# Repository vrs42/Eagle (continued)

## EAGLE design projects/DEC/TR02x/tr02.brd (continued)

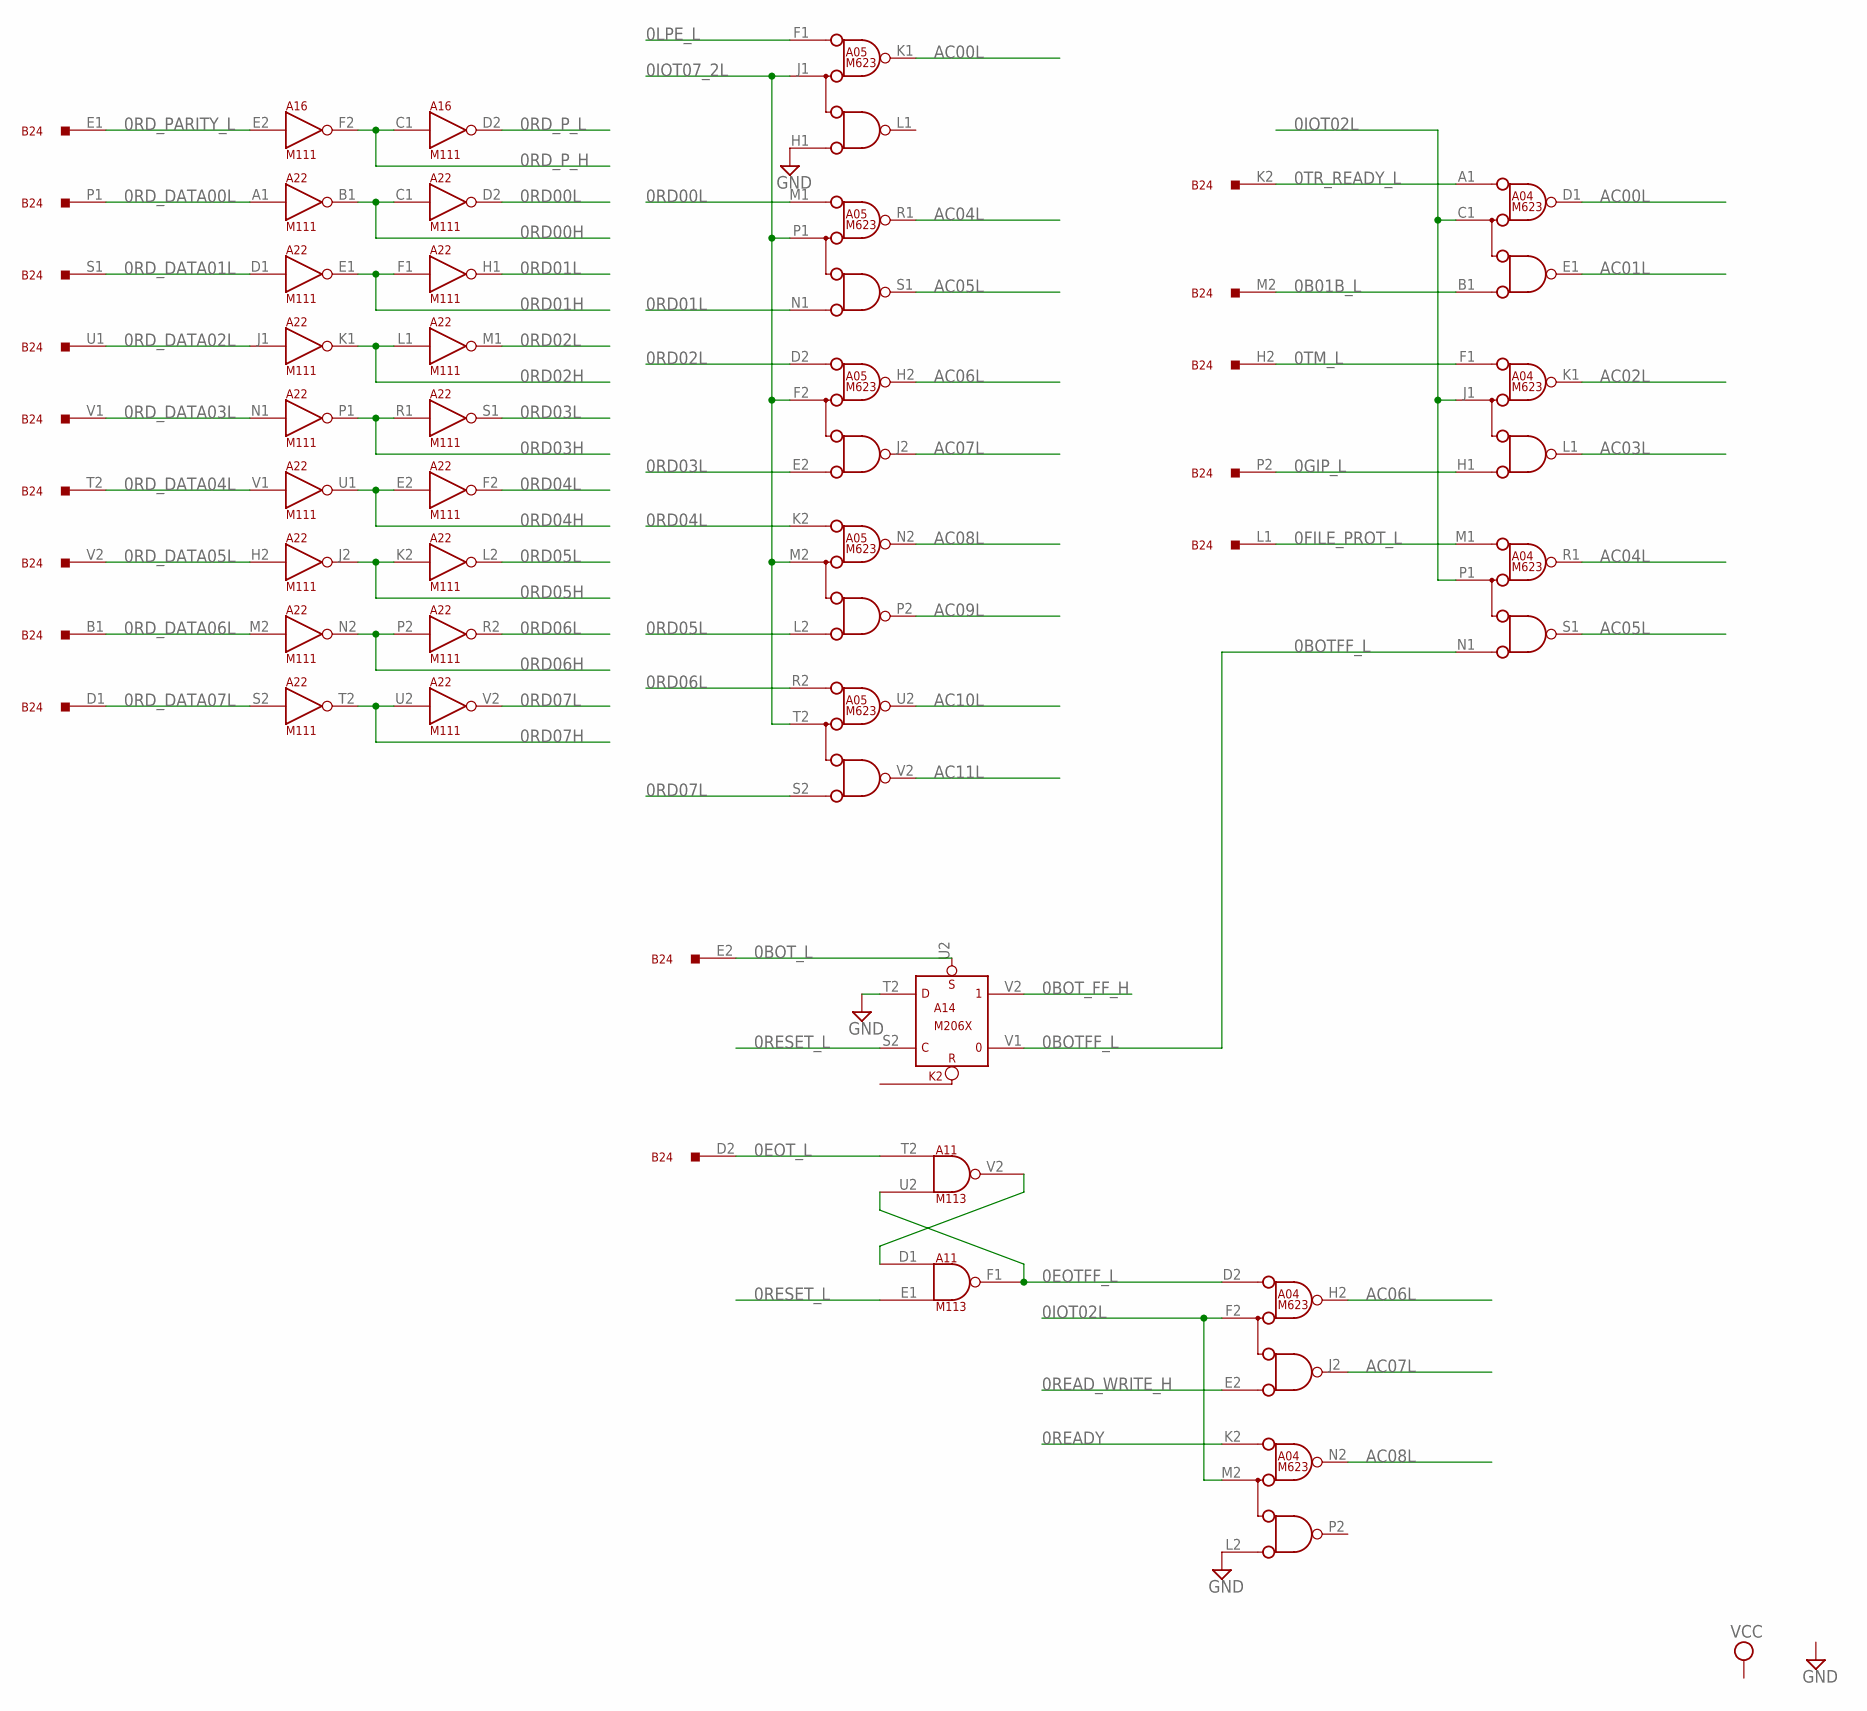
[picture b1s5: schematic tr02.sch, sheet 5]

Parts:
A04, A05: M623; H807
A11: M113; H807
A14: M206X; H807
A16, A22: M111; H807
B24: G784; H807

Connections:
0B01B_L: A04.B1 (B), B24.M2
0BOTFF_L: A04.N1 (B), A14.V1 (0)
0BOT_FF_H: A14.V2 (1); also elsewhere on the board
0BOT_L: A14.U2 (S), B24.E2; also elsewhere on the board
0EOTFF_L: A04.D2 (A), A11.F1 (OUT), A11.U2 (IN2)
0EOT_L: A11.T2 (IN1), B24.D2
0FILE_PROT_L: A04.M1 (A), B24.L1
0GIP_L: A04.H1 (B), B24.P2; also elsewhere on the board
0IOT02L: A04.C1 (C), A04.F2 (C), A04.J1 (C), A04.M2 (C), A04.P1 (C); also elsewhere on the board
0IOT07_2L: A05.F2 (C), A05.J1 (C), A05.M2 (C), A05.P1 (C), A05.T2 (C); also elsewhere on the board
0LPE_L: A05.F1 (A); also elsewhere on the board
0RD00H: A22.B1 (OUT), A22.C1 (IN); also elsewhere on the board
0RD00L: A05.M1 (A), A22.D2 (OUT); also elsewhere on the board
0RD01H: A22.E1 (OUT), A22.F1 (IN); also elsewhere on the board
0RD01L: A05.N1 (B), A22.H1 (OUT); also elsewhere on the board
0RD02H: A22.K1 (OUT), A22.L1 (IN); also elsewhere on the board
0RD02L: A05.D2 (A), A22.M1 (OUT); also elsewhere on the board
0RD03H: A22.P1 (OUT), A22.R1 (IN); also elsewhere on the board
0RD03L: A05.E2 (B), A22.S1 (OUT); also elsewhere on the board
0RD04H: A22.E2 (IN), A22.U1 (OUT); also elsewhere on the board
0RD04L: A05.K2 (A), A22.F2 (OUT); also elsewhere on the board
0RD05H: A22.J2 (OUT), A22.K2 (IN); also elsewhere on the board
0RD05L: A05.L2 (B), A22.L2 (OUT); also elsewhere on the board
0RD06H: A22.N2 (OUT), A22.P2 (IN); also elsewhere on the board
0RD06L: A05.R2 (A), A22.R2 (OUT); also elsewhere on the board
0RD07H: A22.T2 (OUT), A22.U2 (IN); also elsewhere on the board
0RD07L: A05.S2 (B), A22.V2 (OUT); also elsewhere on the board
0RD_DATA00L: A22.A1 (IN), B24.P1
0RD_DATA01L: A22.D1 (IN), B24.S1
0RD_DATA02L: A22.J1 (IN), B24.U1
0RD_DATA03L: A22.N1 (IN), B24.V1
0RD_DATA04L: A22.V1 (IN), B24.T2
0RD_DATA05L: A22.H2 (IN), B24.V2
0RD_DATA06L: A22.M2 (IN), B24.B1
0RD_DATA07L: A22.S2 (IN), B24.D1
0RD_PARITY_L: A16.E2 (IN), B24.E1
0RD_P_H: A16.C1 (IN), A16.F2 (OUT); also elsewhere on the board
0RD_P_L: A16.D2 (OUT)
0READY: A04.K2 (A)
0READ_WRITE_H: A04.E2 (B); also elsewhere on the board
0RESET_L: A11.E1 (IN2), A14.S2 (C); also elsewhere on the board
0TM_L: A04.F1 (A), B24.H2
0TR_READY_L: A04.A1 (A), B24.K2; also elsewhere on the board
AC00L: A04.D1 (D), A05.K1 (D); also elsewhere on the board
AC01L: A04.E1 (E); also elsewhere on the board
AC02L: A04.K1 (D); also elsewhere on the board
AC03L: A04.L1 (E); also elsewhere on the board
AC04L: A04.R1 (D), A05.R1 (D); also elsewhere on the board
AC05L: A04.S1 (E), A05.S1 (E); also elsewhere on the board
AC06L: A04.H2 (D), A05.H2 (D); also elsewhere on the board
AC07L: A04.J2 (E), A05.J2 (E); also elsewhere on the board
AC08L: A04.N2 (D), A05.N2 (D); also elsewhere on the board
AC09L: A05.P2 (E); also elsewhere on the board
AC10L: A05.U2 (D); also elsewhere on the board
AC11L: A05.V2 (E); also elsewhere on the board
GND: A04.C2 (GND), A04.L2 (B), A04.T1 (GND), A04.U1 (GND), A04.V1 (GND), A05.C2 (GND), A05.H1 (B), A05.T1 (GND), A05.U1 (GND), A05.V1 (GND), A11.C2 (GND), A11.T1 (GND), A14.C2 (GND), A14.T1 (GND), A14.T2 (D), A16.C2 (GND), A16.T1 (GND), A22.C2 (GND), A22.T1 (GND); also elsewhere on the board
unnamed: A11.D1 (IN1), A11.V2 (OUT)
VCC: A04.A2 (VCC), A05.A2 (VCC), A11.A2 (VCC), A14.A2 (VCC), A16.A2 (VCC), A22.A2 (VCC); also elsewhere on the board

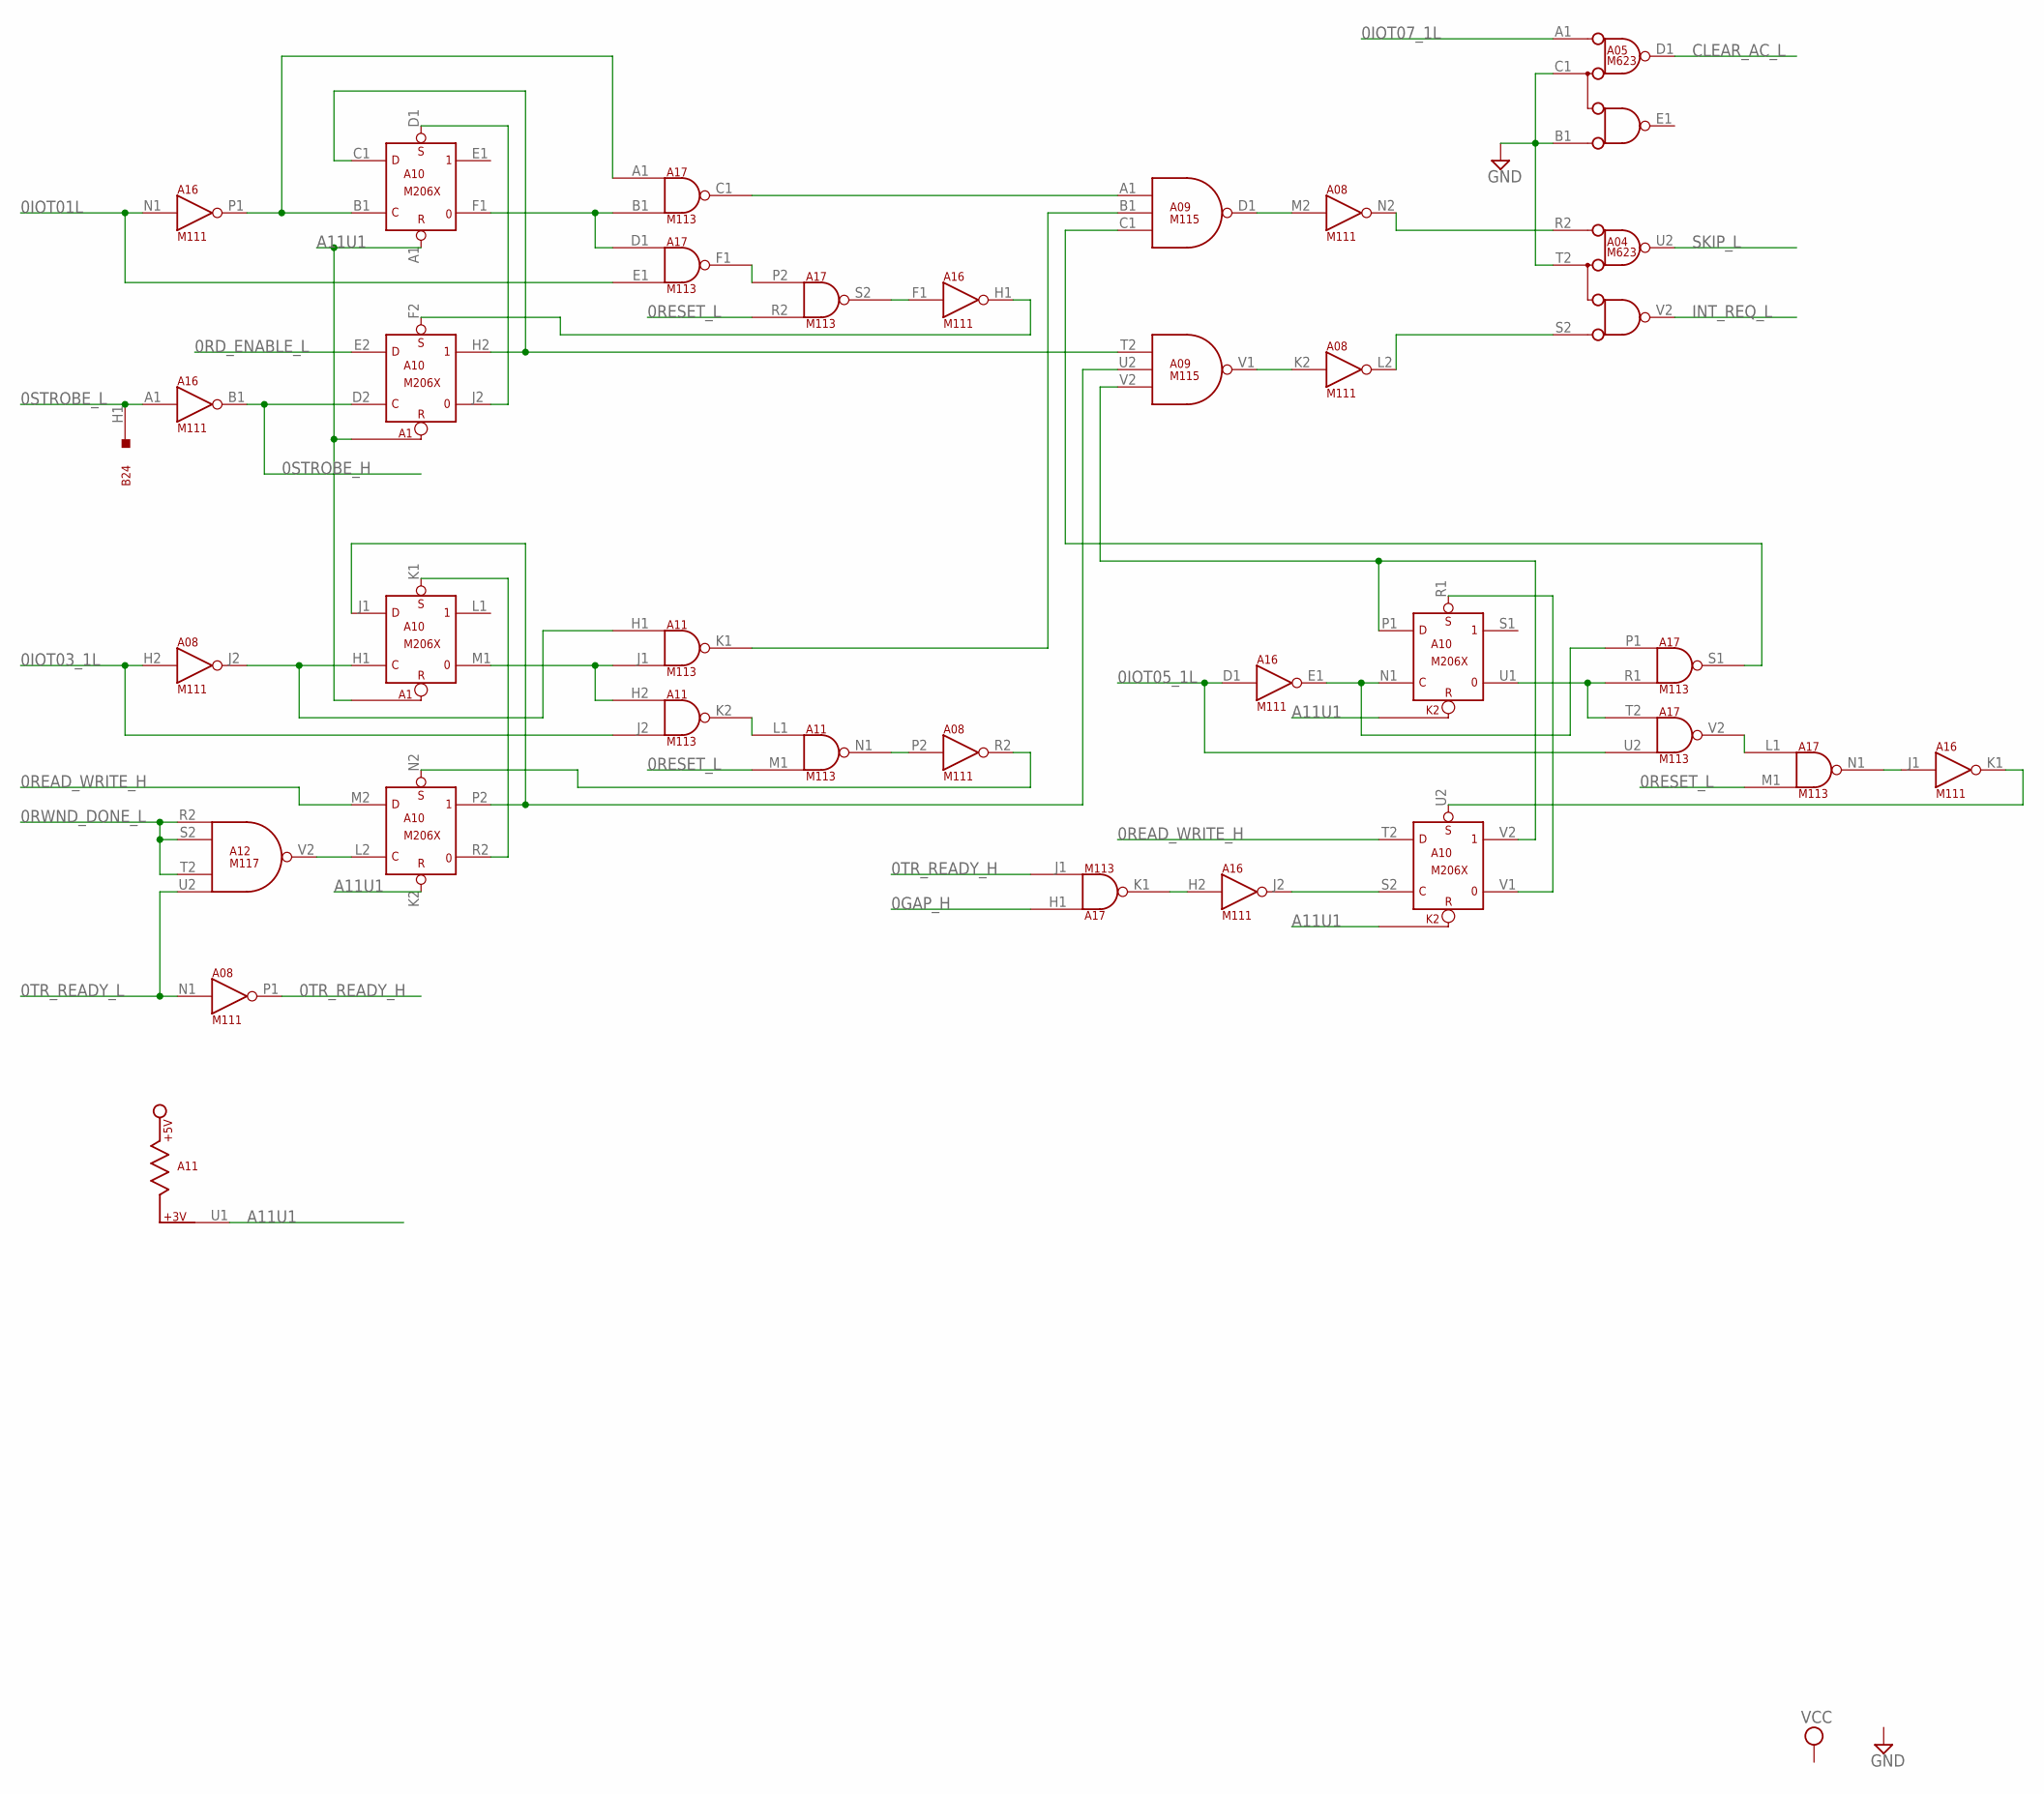
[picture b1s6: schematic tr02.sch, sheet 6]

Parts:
A04, A05: M623; H807
A08, A16: M111; H807
A09: M115; H807
A10: M206X; H807
A11, A17: M113; H807
A12: M117; H807
B24: G784; H807

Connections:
0GAP_H: A17.H1 (IN1); also elsewhere on the board
0IOT01L: A16.N1 (IN), A17.E1 (IN2); also elsewhere on the board
0IOT03_1L: A08.H2 (IN), A11.J2 (IN2); also elsewhere on the board
0IOT05_1L: A16.D1 (IN), A17.U2 (IN2); also elsewhere on the board
0IOT07_1L: A05.A1 (A); also elsewhere on the board
0RD_ENABLE_L: A10.E2 (D); also elsewhere on the board
0READ_WRITE_H: A10.M2 (D), A10.T2 (D); also elsewhere on the board
0RESET_L: A11.M1 (IN2), A17.M1 (IN2), A17.R2 (IN2); also elsewhere on the board
0RWND_DONE_L: A12.R2 (IN1), A12.S2 (IN2), A12.T2 (IN3); also elsewhere on the board
0STROBE_H: A10.D2 (C), A16.B1 (OUT)
0STROBE_L: A16.A1 (IN), B24.H1; also elsewhere on the board
0TR_READY_H: A08.P1 (OUT), A17.J1 (IN2)
0TR_READY_L: A08.N1 (IN), A12.U2 (IN4); also elsewhere on the board
A11U1: A10.A1 (R), A10.K2 (R), A11.U1
CLEAR_AC_L: A05.D1 (D); also elsewhere on the board
GND: A04.C2 (GND), A04.T1 (GND), A04.T2 (C), A04.U1 (GND), A04.V1 (GND), A05.B1 (B), A05.C1 (C), A05.C2 (GND), A05.T1 (GND), A05.U1 (GND), A05.V1 (GND), A08.C2 (GND), A08.T1 (GND), A09.C2 (GND), A09.T1 (GND), A10.C2 (GND), A10.T1 (GND), A11.C2 (GND), A11.T1 (GND), A12.C2 (GND), A12.T1 (GND), A16.C2 (GND), A16.T1 (GND), A17.C2 (GND), A17.T1 (GND); also elsewhere on the board
INT_REQ_L: A04.V2 (E); also elsewhere on the board
unnamed: A10.B1 (C), A16.P1 (OUT), A17.A1 (IN1)
unnamed: A16.F1 (IN), A17.S2 (OUT)
unnamed: A08.J2 (OUT), A10.H1 (C), A11.H1 (IN1)
unnamed: A10.L2 (C), A12.V2 (OUT)
unnamed: A10.D1 (S), A10.J2 (0)
unnamed: A09.T2 (IN1), A10.C1 (D), A10.H2 (1)
unnamed: A10.F2 (S), A16.H1 (OUT)
unnamed: A10.F1 (0), A17.B1 (IN2), A17.D1 (IN1)
unnamed: A17.F1 (OUT), A17.P2 (IN1)
unnamed: A09.A1 (IN1), A17.C1 (OUT)
unnamed: A10.K1 (S), A10.R2 (0)
unnamed: A09.U2 (IN2), A10.J1 (D), A10.P2 (1)
unnamed: A10.M1 (0), A11.H2 (IN1), A11.J1 (IN2)
unnamed: A16.H2 (IN), A17.K1 (OUT)
unnamed: A09.B1 (IN2), A11.K1 (OUT)
unnamed: A11.K2 (OUT), A11.L1 (IN1)
unnamed: A08.P2 (IN), A11.N1 (OUT)
unnamed: A08.R2 (OUT), A10.N2 (S)
unnamed: A08.K2 (IN), A09.V1 (OUT)
unnamed: A08.M2 (IN), A09.D1 (OUT)
unnamed: A10.S2 (C), A16.J2 (OUT)
unnamed: A10.N1 (C), A16.E1 (OUT), A17.P1 (IN1)
unnamed: A04.R2 (A), A08.N2 (OUT)
unnamed: A04.S2 (B), A08.L2 (OUT)
unnamed: A09.V2 (IN3), A10.P1 (D), A10.V2 (1)
unnamed: A10.R1 (S), A10.V1 (0)
unnamed: A10.U2 (S), A16.K1 (OUT)
unnamed: A10.U1 (0), A17.R1 (IN2), A17.T2 (IN1)
unnamed: A17.L1 (IN1), A17.V2 (OUT)
unnamed: A16.J1 (IN), A17.N1 (OUT)
unnamed: A09.C1 (IN3), A17.S1 (OUT)
SKIP_L: A04.U2 (D); also elsewhere on the board
VCC: A04.A2 (VCC), A05.A2 (VCC), A08.A2 (VCC), A09.A2 (VCC), A10.A2 (VCC), A11.A2 (VCC), A12.A2 (VCC), A16.A2 (VCC), A17.A2 (VCC); also elsewhere on the board

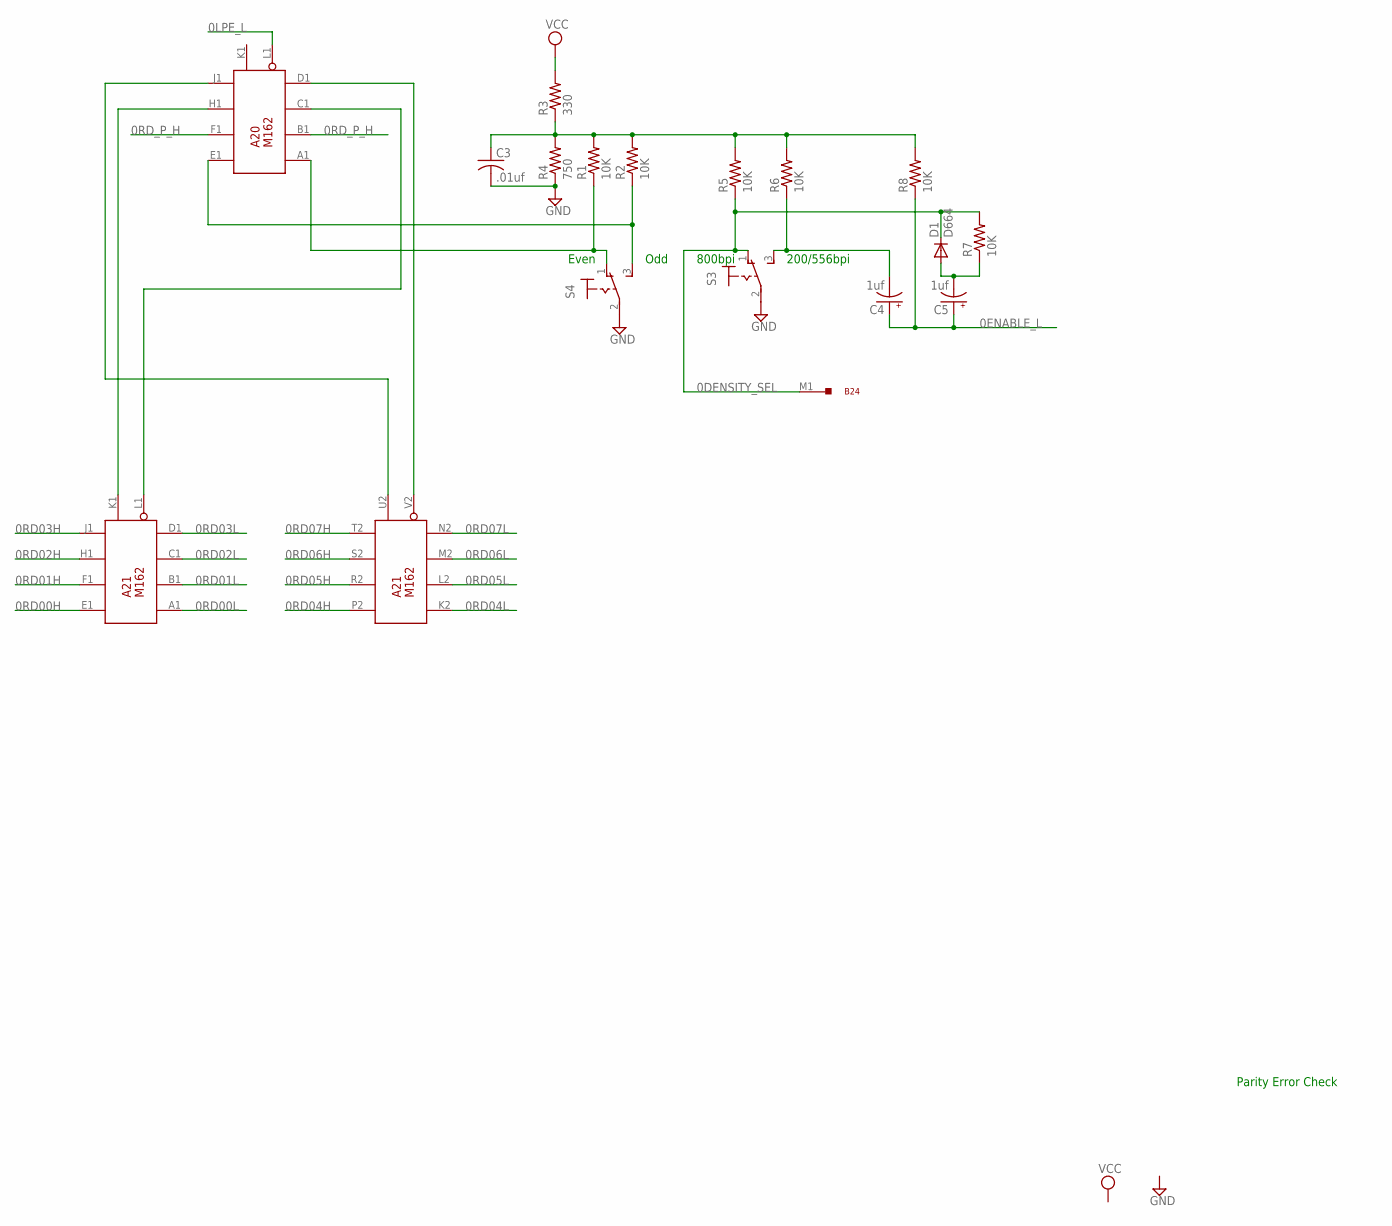
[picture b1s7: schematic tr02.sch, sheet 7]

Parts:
A20, A21: M162; H807
B24: G784; H807
C3: .01uf; C050-025X075
C4, C5: 1uf; E22-6
D1: D664; DO35-10
R1, R2, R5, R6, R7, R8: 10K; 0207/10
R3: 330; 0207/10
R4: 750; 0207/10
S3, S4: 320-916

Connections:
0DENSITY_SEL: B24.M1, D1.C, R5.1, R7.2, S3.1 (O)
0ENABLE_L: C4.+, C5.+, R8.1; also elsewhere on the board
0LPE_L: A20.L1 (EVEN); also elsewhere on the board
0RD00H: A21.E1 (1A); also elsewhere on the board
0RD00L: A21.A1 (1B); also elsewhere on the board
0RD01H: A21.F1 (2A); also elsewhere on the board
0RD01L: A21.B1 (2B); also elsewhere on the board
0RD02H: A21.H1 (4A); also elsewhere on the board
0RD02L: A21.C1 (4B); also elsewhere on the board
0RD03H: A21.J1 (8A); also elsewhere on the board
0RD03L: A21.D1 (8B); also elsewhere on the board
0RD04H: A21.P2 (1A); also elsewhere on the board
0RD04L: A21.K2 (1B); also elsewhere on the board
0RD05H: A21.R2 (2A); also elsewhere on the board
0RD05L: A21.L2 (2B); also elsewhere on the board
0RD06H: A21.S2 (4A); also elsewhere on the board
0RD06L: A21.M2 (4B); also elsewhere on the board
0RD07H: A21.T2 (8A); also elsewhere on the board
0RD07L: A21.N2 (8B); also elsewhere on the board
0RD_P_H: A20.B1 (2B), A20.F1 (2A); also elsewhere on the board
GND: A20.C2 (GND), A20.T1 (GND), A21.C2 (GND), A21.T1 (GND), C3.2, R4.1, S3.2, S4.2; also elsewhere on the board
unnamed: A20.E1 (1A), R2.1, S4.3 (S)
unnamed: A20.A1 (1B), R1.1, S4.1 (O)
unnamed: A20.C1 (4B), A21.L1 (EVEN)
unnamed: A20.J1 (8A), A21.U2 (ODD)
unnamed: C5.-, D1.A, R7.1
unnamed: A20.H1 (4A), A21.K1 (ODD)
unnamed: A20.D1 (8B), A21.V2 (EVEN)
unnamed: C3.1, R1.2, R2.2, R3.1, R4.2, R5.2, R6.2, R8.2
unnamed: C4.-, R6.1, S3.3 (S)
VCC: A20.A2 (VCC), A21.A2 (VCC), R3.2; also elsewhere on the board

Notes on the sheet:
Even
Odd
800bpi
200/556bpi
Parity Error Check

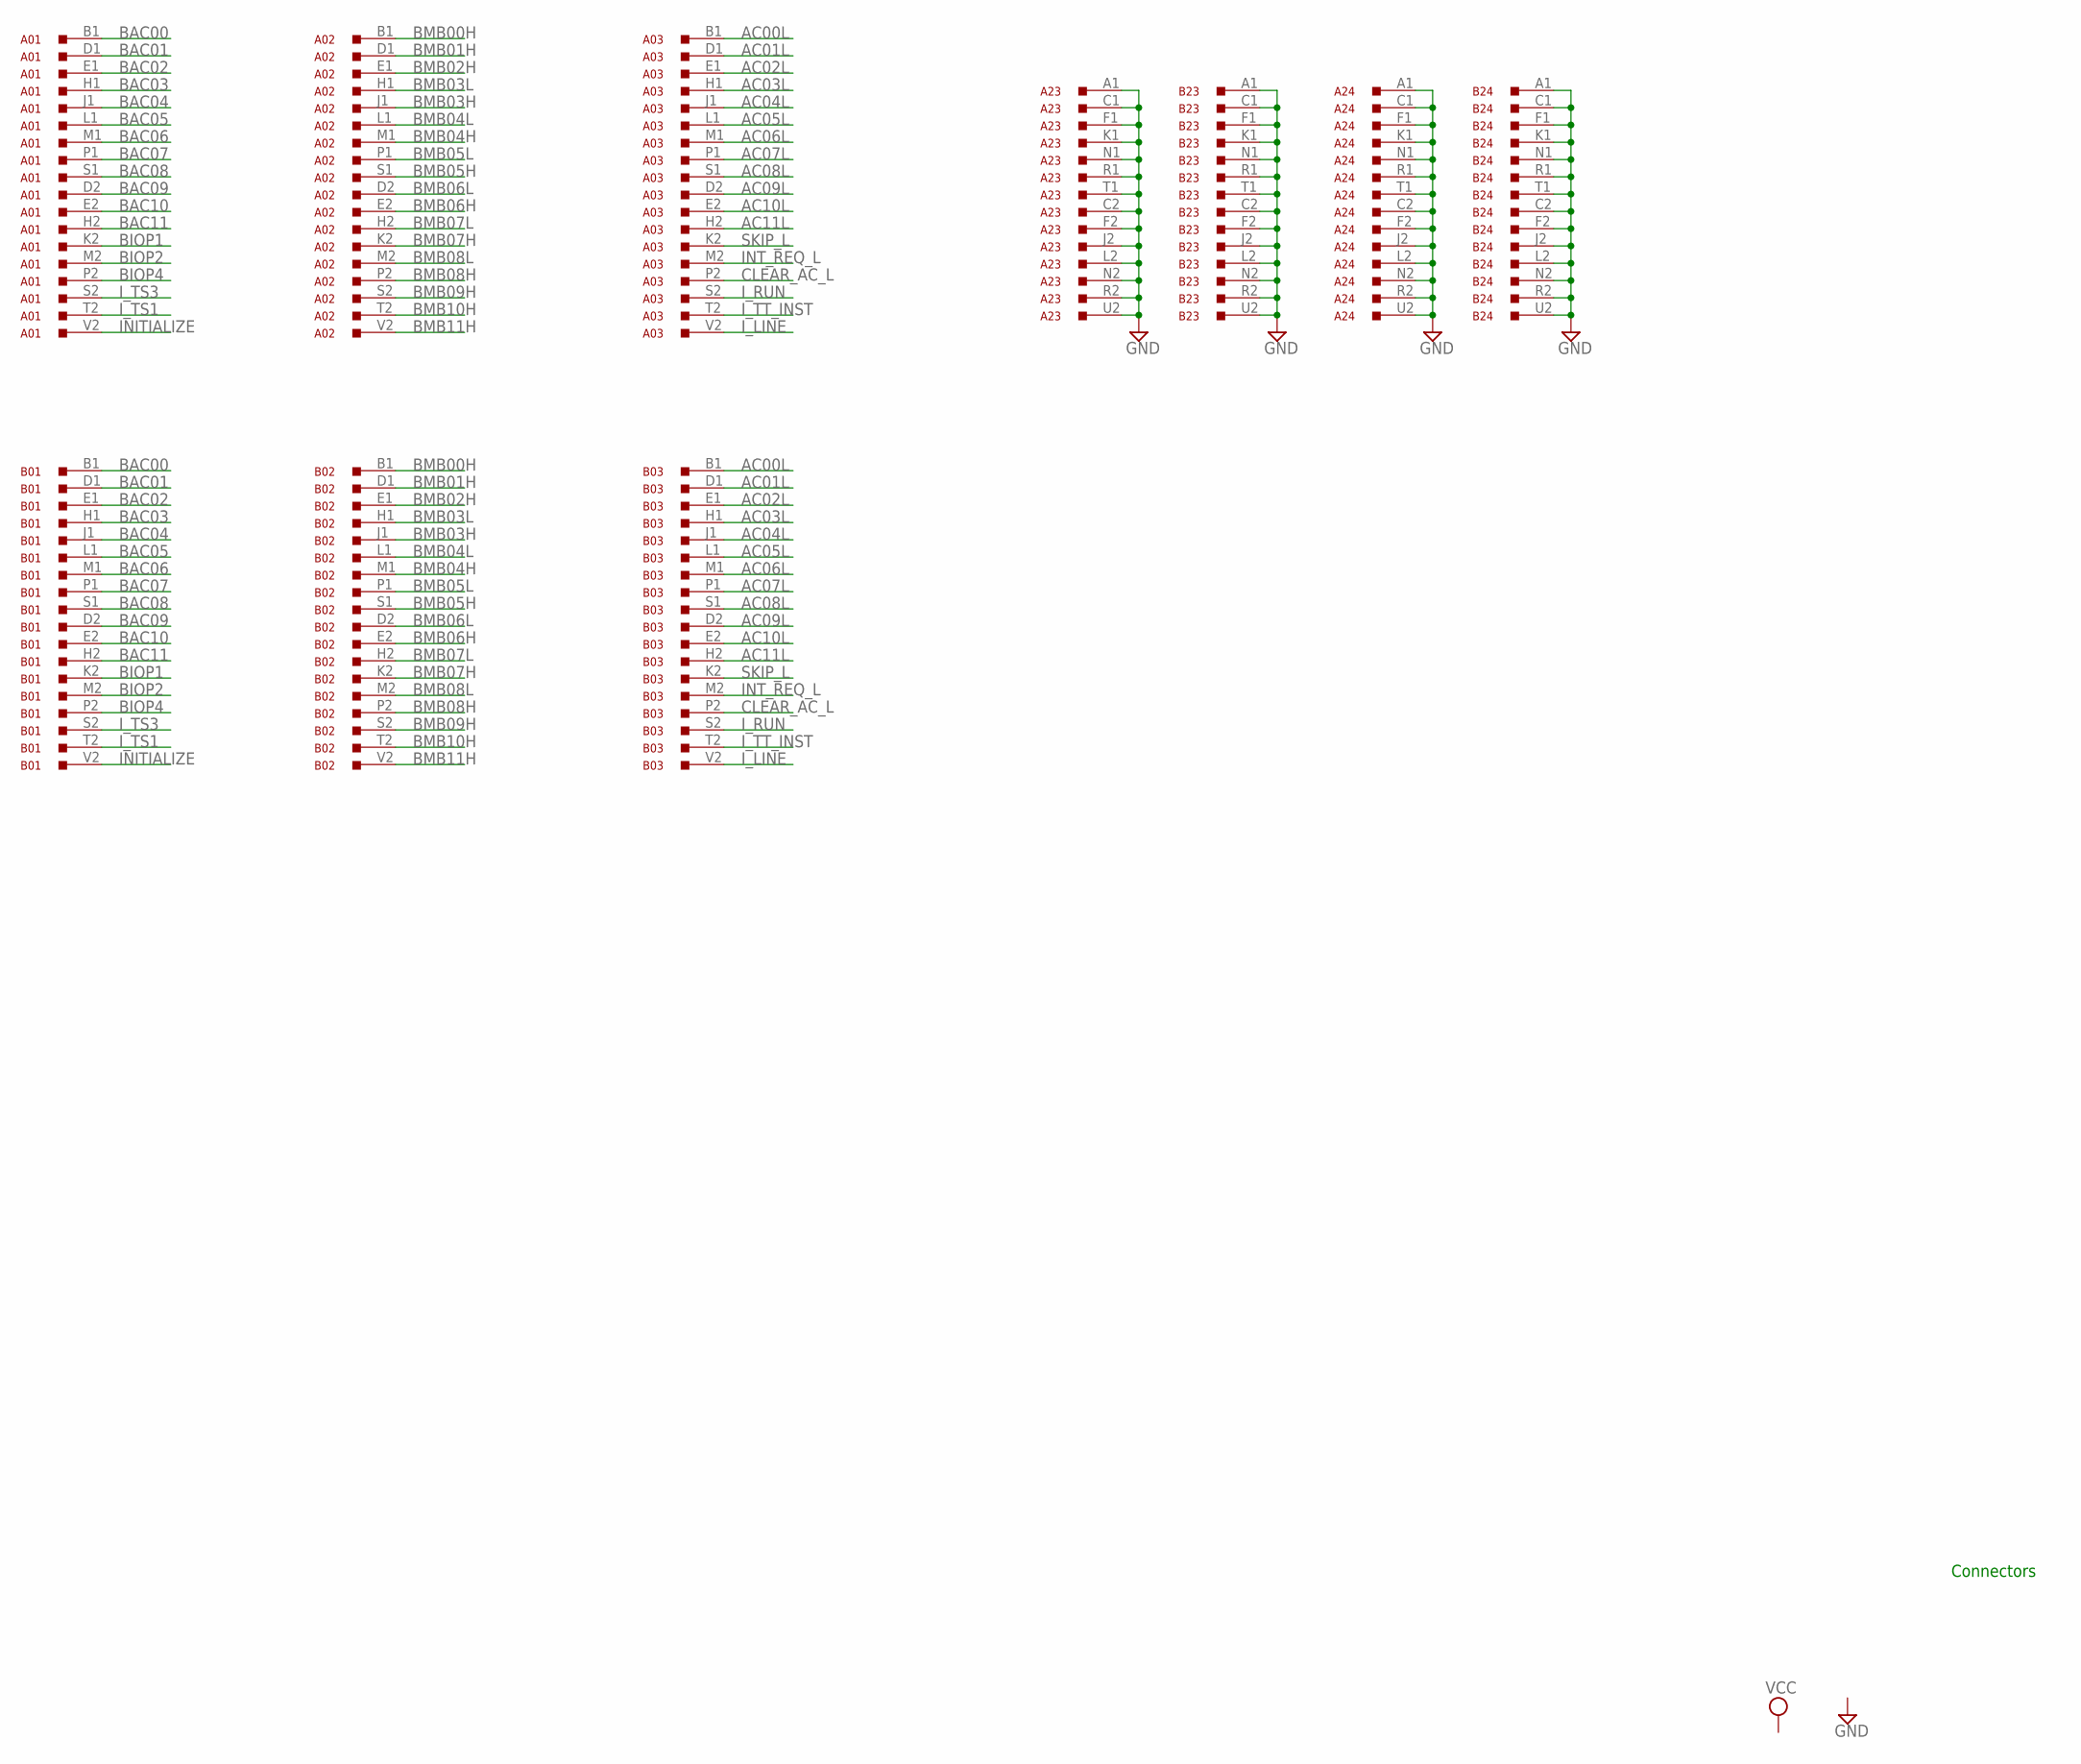
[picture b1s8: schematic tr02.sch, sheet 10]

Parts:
A01, A02, A03: M903; H807
A23, A24: G784; H807
B01, B02, B03: M903; H807
B23, B24: G784; H807

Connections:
AC00L: A03.B1, B03.B1; also elsewhere on the board
AC01L: A03.D1, B03.D1; also elsewhere on the board
AC02L: A03.E1, B03.E1; also elsewhere on the board
AC03L: A03.H1, B03.H1; also elsewhere on the board
AC04L: A03.J1, B03.J1; also elsewhere on the board
AC05L: A03.L1, B03.L1; also elsewhere on the board
AC06L: A03.M1, B03.M1; also elsewhere on the board
AC07L: A03.P1, B03.P1; also elsewhere on the board
AC08L: A03.S1, B03.S1; also elsewhere on the board
AC09L: A03.D2, B03.D2; also elsewhere on the board
AC10L: A03.E2, B03.E2; also elsewhere on the board
AC11L: A03.H2, B03.H2; also elsewhere on the board
BAC00: A01.B1, B01.B1; also elsewhere on the board
BAC01: A01.D1, B01.D1; also elsewhere on the board
BAC02: A01.E1, B01.E1; also elsewhere on the board
BAC03: A01.H1, B01.H1
BAC04: A01.J1, B01.J1; also elsewhere on the board
BAC05: A01.L1, B01.L1; also elsewhere on the board
BAC06: A01.M1, B01.M1; also elsewhere on the board
BAC07: A01.P1, B01.P1; also elsewhere on the board
BAC08: A01.S1, B01.S1; also elsewhere on the board
BAC09: A01.D2, B01.D2; also elsewhere on the board
BAC10: A01.E2, B01.E2; also elsewhere on the board
BAC11: A01.H2, B01.H2; also elsewhere on the board
BIOP1: A01.K2, B01.K2; also elsewhere on the board
BIOP2: A01.M2, B01.M2; also elsewhere on the board
BIOP4: A01.P2, B01.P2; also elsewhere on the board
BMB00H: A02.B1, B02.B1
BMB01H: A02.D1, B02.D1
BMB02H: A02.E1, B02.E1
BMB03H: A02.J1, B02.J1; also elsewhere on the board
BMB03L: A02.H1, B02.H1
BMB04H: A02.M1, B02.M1; also elsewhere on the board
BMB04L: A02.L1, B02.L1
BMB05H: A02.S1, B02.S1; also elsewhere on the board
BMB05L: A02.P1, B02.P1
BMB06H: A02.E2, B02.E2
BMB06L: A02.D2, B02.D2; also elsewhere on the board
BMB07H: A02.K2, B02.K2
BMB07L: A02.H2, B02.H2; also elsewhere on the board
BMB08H: A02.P2, B02.P2; also elsewhere on the board
BMB08L: A02.M2, B02.M2; also elsewhere on the board
BMB09H: A02.S2, B02.S2; also elsewhere on the board
BMB10H: A02.T2, B02.T2; also elsewhere on the board
BMB11H: A02.V2, B02.V2; also elsewhere on the board
CLEAR_AC_L: A03.P2, B03.P2; also elsewhere on the board
GND: A01.A1 (GND), A01.C1 (GND), A01.C2 (GND), A01.F1 (GND), A01.F2 (GND), A01.J2 (GND), A01.K1 (GND), A01.L2 (GND), A01.N1 (GND), A01.N2 (GND), A01.R1 (GND), A01.R2 (GND), A01.T1 (GND), A01.U2 (GND), A02.A1 (GND), A02.C1 (GND), A02.C2 (GND), A02.F1 (GND), A02.F2 (GND), A02.J2 (GND), A02.K1 (GND), A02.L2 (GND), A02.N1 (GND), A02.N2 (GND), A02.R1 (GND), A02.R2 (GND), A02.T1 (GND), A02.U2 (GND), A03.A1 (GND), A03.C1 (GND), A03.C2 (GND), A03.F1 (GND), A03.F2 (GND), A03.J2 (GND), A03.K1 (GND), A03.L2 (GND), A03.N1 (GND), A03.N2 (GND), A03.R1 (GND), A03.R2 (GND), A03.T1 (GND), A03.U2 (GND), A23.A1, A23.C1, A23.C2, A23.F1, A23.F2, A23.J2, A23.K1, A23.L2, A23.N1, A23.N2, A23.R1, A23.R2, A23.T1, A23.U2, A24.A1, A24.C1, A24.C2, A24.F1, A24.F2, A24.J2, A24.K1, A24.L2, A24.N1, A24.N2, A24.R1, A24.R2, A24.T1, A24.U2, B01.A1 (GND), B01.C1 (GND), B01.C2 (GND), B01.F1 (GND), B01.F2 (GND), B01.J2 (GND), B01.K1 (GND), B01.L2 (GND), B01.N1 (GND), B01.N2 (GND), B01.R1 (GND), B01.R2 (GND), B01.T1 (GND), B01.U2 (GND), B02.A1 (GND), B02.C1 (GND), B02.C2 (GND), B02.F1 (GND), B02.F2 (GND), B02.J2 (GND), B02.K1 (GND), B02.L2 (GND), B02.N1 (GND), B02.N2 (GND), B02.R1 (GND), B02.R2 (GND), B02.T1 (GND), B02.U2 (GND), B03.A1 (GND), B03.C1 (GND), B03.C2 (GND), B03.F1 (GND), B03.F2 (GND), B03.J2 (GND), B03.K1 (GND), B03.L2 (GND), B03.N1 (GND), B03.N2 (GND), B03.R1 (GND), B03.R2 (GND), B03.T1 (GND), B03.U2 (GND), B23.A1, B23.C1, B23.C2, B23.F1, B23.F2, B23.J2, B23.K1, B23.L2, B23.N1, B23.N2, B23.R1, B23.R2, B23.T1, B23.U2, B24.A1, B24.C1, B24.C2, B24.F1, B24.F2, B24.J2, B24.K1, B24.L2, B24.N1, B24.N2, B24.R1, B24.R2, B24.T1, B24.U2; also elsewhere on the board
INITIALIZE: A01.V2, B01.V2; also elsewhere on the board
INT_REQ_L: A03.M2, B03.M2; also elsewhere on the board
I_LINE: A03.V2, B03.V2
I_RUN: A03.S2, B03.S2
I_TS1: A01.T2, B01.T2
I_TS3: A01.S2, B01.S2
I_TT_INST: A03.T2, B03.T2
SKIP_L: A03.K2, B03.K2; also elsewhere on the board

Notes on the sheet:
Connectors

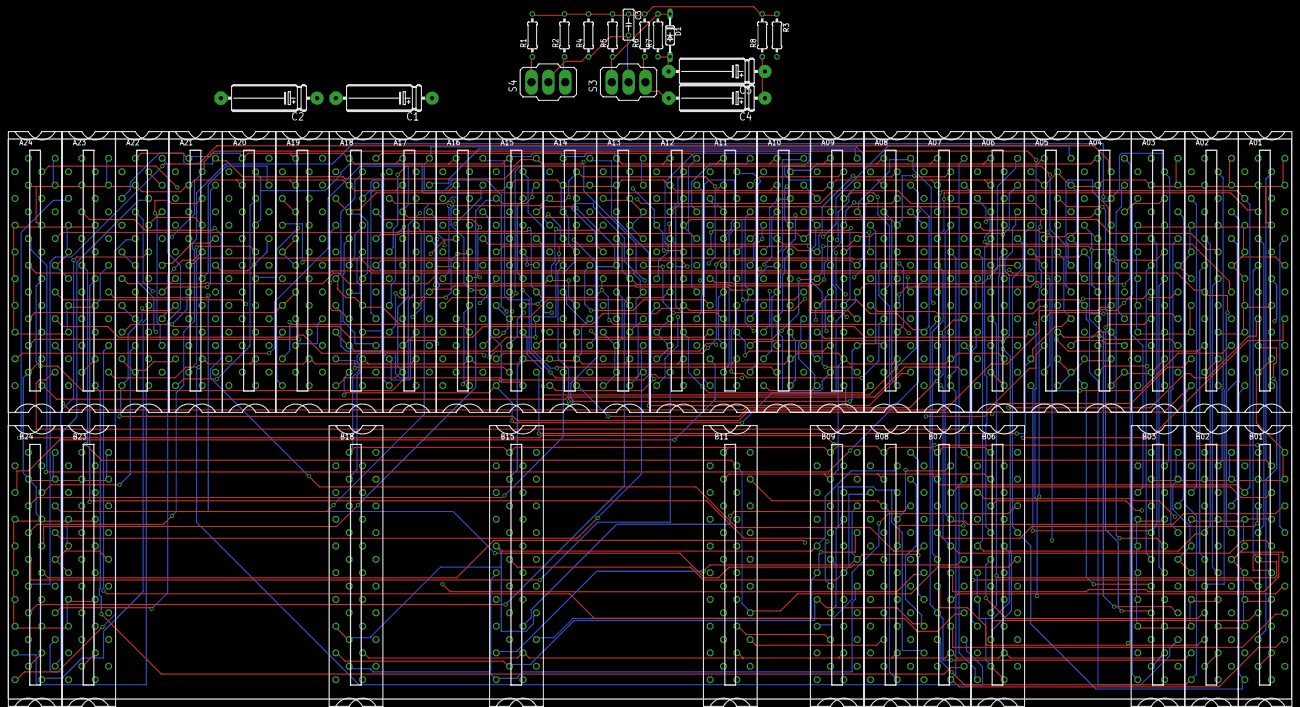
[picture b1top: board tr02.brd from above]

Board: 4 copper layers, 304.8 x 133.0 mm, 52 parts (0 on the bottom side), 257 nets.
